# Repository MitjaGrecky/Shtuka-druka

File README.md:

# Shtuka Druka

An open, standalone desktop music instrument: synthesizer, sampler and DAW in one box.
The idea is improvising with sound from everywhere: capture audio from any source,
then shape it with filters and effects.

Status: design phase. Panel layout v7, enclosure, I/O, audio chain and compute platform are decided.
First board: M1 screen knobs module (being routed). Next: W1 Levels, then a 1:1 cardboard mockup.

## What is here

| Folder | Contents |
|---|---|
| `docs/ru/` | Research and design documents (Russian). Start with `README.md` (map of documents) and `decisions/README.md` — the single source of truth for every decision, split by topic |
| `bench/` | CPU benchmark: how many reference tracks a processor can run at 48 kHz / 128 samples |
| `mockup/` | 1:1 cardboard mockup templates (A4, PDF) and the script that generates them |
| `model3d/` | Interactive 3D model of panel v7, built from `mockup/layout/layout_v7.json` (open `index.html` in a browser; rebuild with `build_model3d_v7.py`) |
| `firmware/protocol/` | Board <-> computer protocol (SDP v0): C header for firmware and host |
| `tools/` | `sdp.py`: reference codec, self-test and frame monitor |
| `hardware/` | KiCad boards, generated from Python (`gen/`), checked by CI: `m1-screen-knobs` (first board), `w1-levels` |
| `notes/handoff.md` | Task queue between the cloud and local Claude sessions (rules in `CLAUDE.md`) |
| `.github/workflows/` | CI: ERC, DRC with schematic parity, BOM, Gerbers for every board on every push |

## Key facts

- 8x8 RGB pad grid, 16+ tracks (target 32-64), endless encoders with LED rings, 10.1" screen at 30 deg
- Body 515 x 460 mm, 68 mm high at the front, 143 mm at the rear, 30 deg slope for the screen, detachable wrist rest
- Inputs: 2 combo XLR/TRS, 2 Hi-Z, phono with RIAA, 8 line inputs, USB audio, 2-4 CV
- Converters: Cirrus Logic Pro (CS5308P/CS5304P ADC, CS4308P DAC), two-path inputs without a preamp chip
- Outputs: Main and Aux (balanced TRS), RCA copy of Main, 2 headphones
- MIDI: 2 in / 4 out DIN, 1 in / 2 out TRS (type A/B switchable); 8 CV/Gate, sync block, Ableton Link
- Compute: x86 on a Mini-ITX board (Intel N100 to start, 8-core upgrade on the same mounts)
- Two RP2350 boards (panel, control) over internal USB; audio board on two xcore.ai, USB Audio Class 2

## Licenses

- Software: GNU AGPL-3.0-or-later (`LICENSE`)
- Hardware: CERN-OHL-S-2.0 (`hardware/LICENSE`)

---

Штука Дрюка — открытый настольный инструмент: синтезатор, сэмплер и DAW в одном корпусе.
Документы проекта на русском лежат в `docs/ru/`, карта документов — `docs/ru/README.md`, все решения — в `docs/ru/decisions/` (начинать с `README.md`).

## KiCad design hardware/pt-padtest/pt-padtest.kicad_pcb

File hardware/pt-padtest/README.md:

# PT — тестовая плата пэдов 4 × 4 (R194, P120)

**Статус: rev 0.1 (26.11.2026) — схема и расстановка, без трассировки.** 2 слоя, 132 × 164 мм, 153 детали. Генераторы: `gen/footprints.py` (электроды и посадки светодиода в общую библиотеку), `gen/design.py`, `gen/make_sch.py`, `gen/make_pcb.py`. Проверки на ПК: ERC 0, DRC 0 ошибок (431 неразведённое), parity 0, `sch_netcheck` 0.

## Пэды: полный перебор 2 × 2 × 2, каждый вариант под ножки V1 и V3

Шаг 28 × 25, поле гребёнок 21 × 17, четыре зоны + общий электрод (рамка с пальцами). Столбцы 1–2 — ножка V1, 3–4 — V3.

| Ряд (спереди назад по плате) | Зоны | Прорезь под свет | Столбцы 1 и 3 | Столбцы 2 и 4 |
|---|---|---|---|---|
| 1 (пэды 1–4) | квадранты | 3,5 × 3,1 («3 мм») | 7 mil | 10 mil |
| 2 (5–8) | квадранты | 3,5 × 4,0 («4 мм») | 7 mil | 10 mil |
| 3 (9–12) | треугольники | 3,5 × 3,1 | 7 mil | 10 mil |
| 4 (13–16) | треугольники | 3,5 × 4,0 | 7 mil | 10 mil |

Проверено скриптом: каждый электрод — один кусок меди, зазор до общего ровно 0,179 / 0,255 мм, площади зон 19,7–22,3 мм². Маска открыта по всему полю, покрытие **ENIG**.

## Электроника

| Блок | Детали |
|---|---|
| Контроллер | Raspberry Pi Pico 2 модулем на штырях (USB); GPIO как на P2: GP0/1 I²C, GP16–19 SPI0, GP20–22 адрес мультиплексоров |
| Чтение 64 зон | как на P2: общий электрод на +3V3A, 10 кОм на зону, 8 × 74HC4051 → ADC128S102 (канал АЦП = мультиплексор, пэды по два: Y0–Y3 и Y4–Y7), 1 кОм + 1 нФ |
| Свет | 16 × GL6028RGB01-B (C51933363), снизу, в прорезь; LP5864, строки SW0–SW2 по 6 пэдов; 5 В от USB |

Прошивка LP5864: Max_Line_Num = 3, режим 1, 125 кГц, PWM_Phase_Shift (Dev_initial = 0x18, `notes/closing/led_noise.md`).

## Отличия от P120 и открытое

- **Отверстие не круглое.** Светодиод реверсивного монтажа стоит в прорези, круг Ø 3/4 мм вместе с ним не помещается. «3 мм» и «4 мм» — прорези 3,1 и 4,0 мм по y при ширине 3,5.
- **Посадка светодиода** — библиотечная EasyEDA/LCSC для C51933363; площадки укорочены с внутренней стороны (x 1,85 → 1,95), чтобы медь отстояла от прорези на 0,2 мм (в библиотеке 0,1). **Даташита нет** (JLC не отдаёт): не подтверждены цвета катодов 1/2/4 (прошивка переназначит), высота корпуса и выступ линзы над платой (дизайнеру: выемка в ножке Ø 6). PDF GL6028RGB01-B — в список пользователю.
- Наличие на 26.11.2026 (JLC): C51933363 ≈ 7100 шт.
- Не разведена; допуски фрезеровки прорезей и поведение XactFSR не проверялись.
- `pcb_geomcheck` пишет «courtyard outside the outline» для пэдов и светодиодов: это внутренние прорези, ложное срабатывание.

License: CERN-OHL-S-2.0 (hardware), AGPL-3.0-or-later (code).

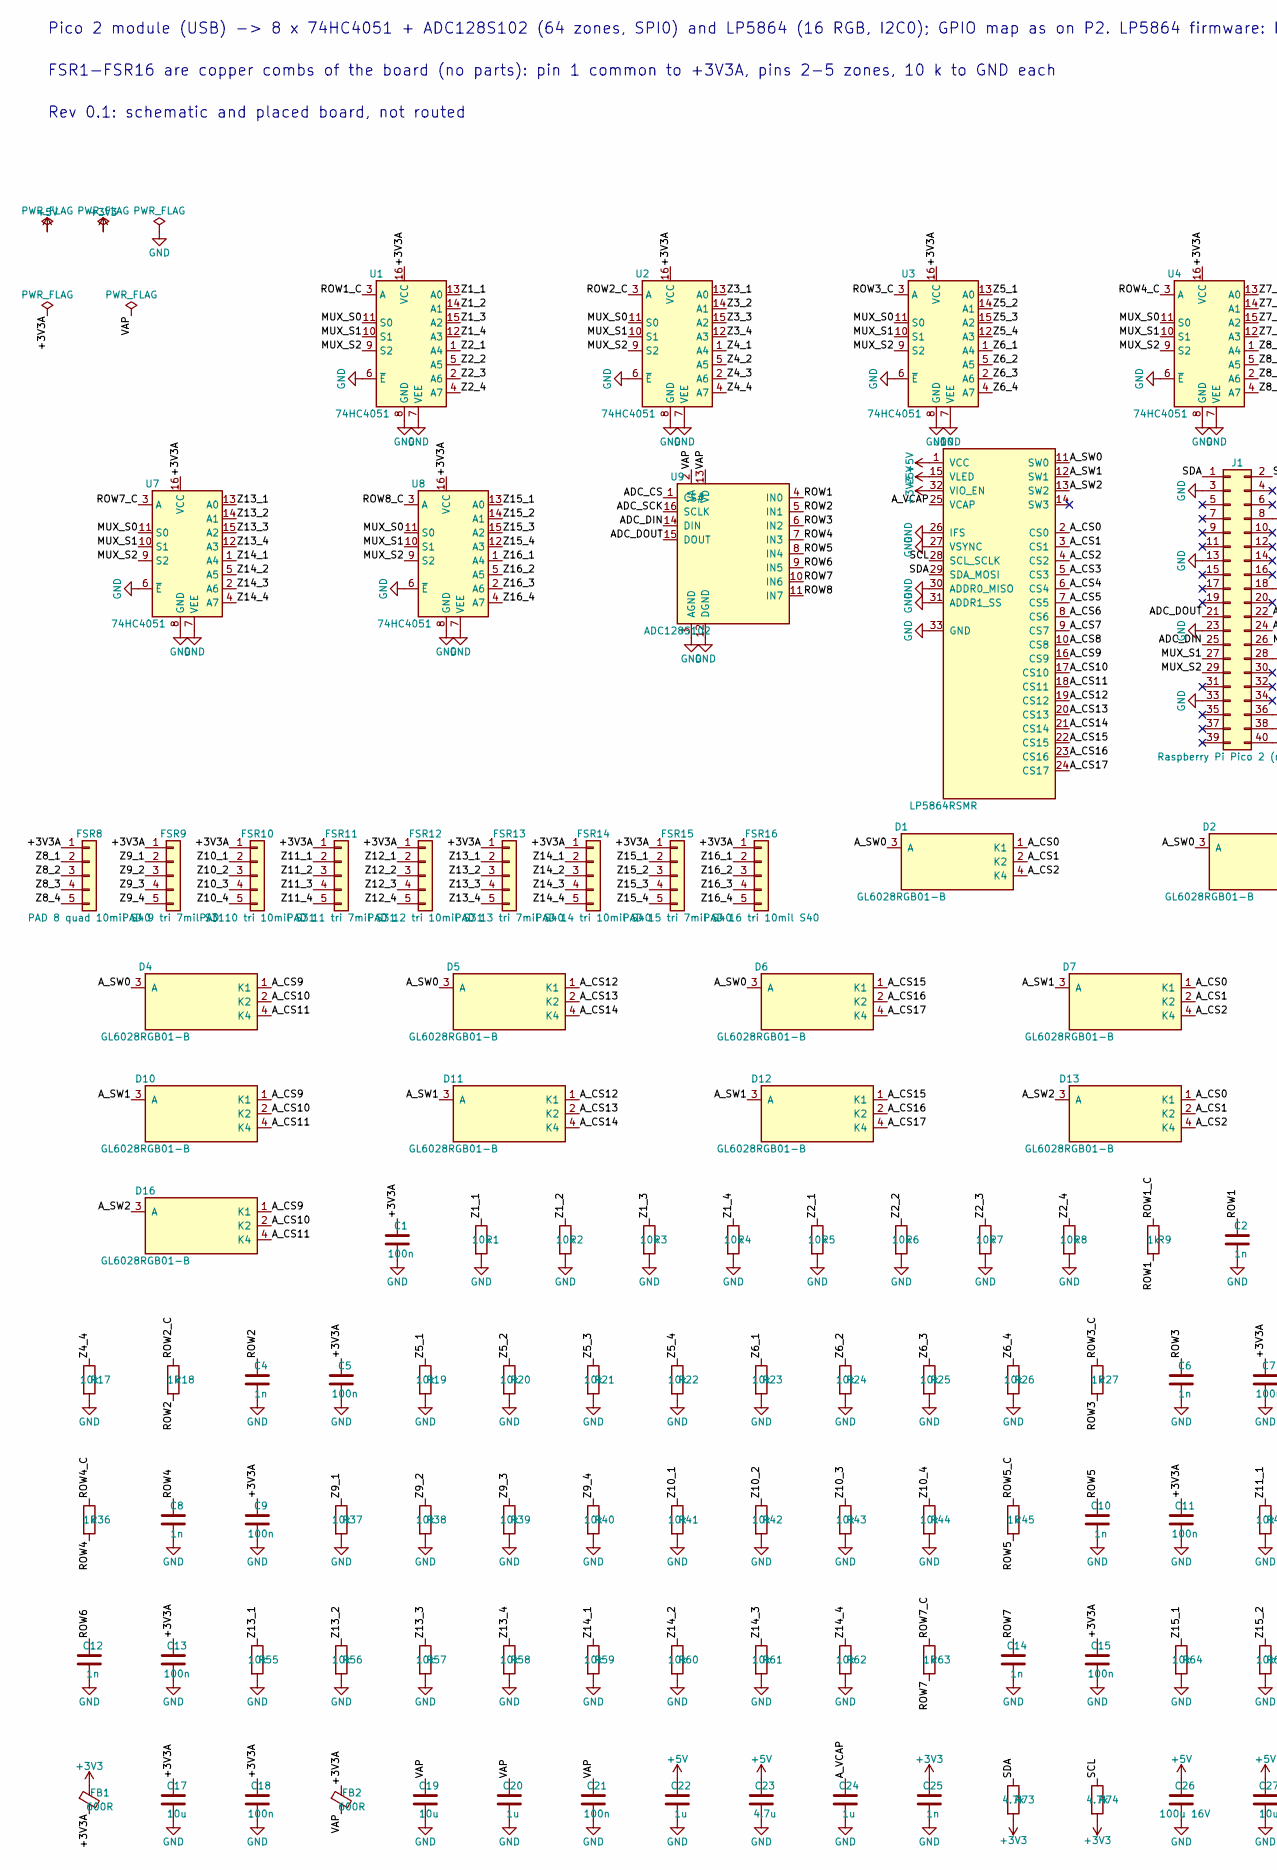
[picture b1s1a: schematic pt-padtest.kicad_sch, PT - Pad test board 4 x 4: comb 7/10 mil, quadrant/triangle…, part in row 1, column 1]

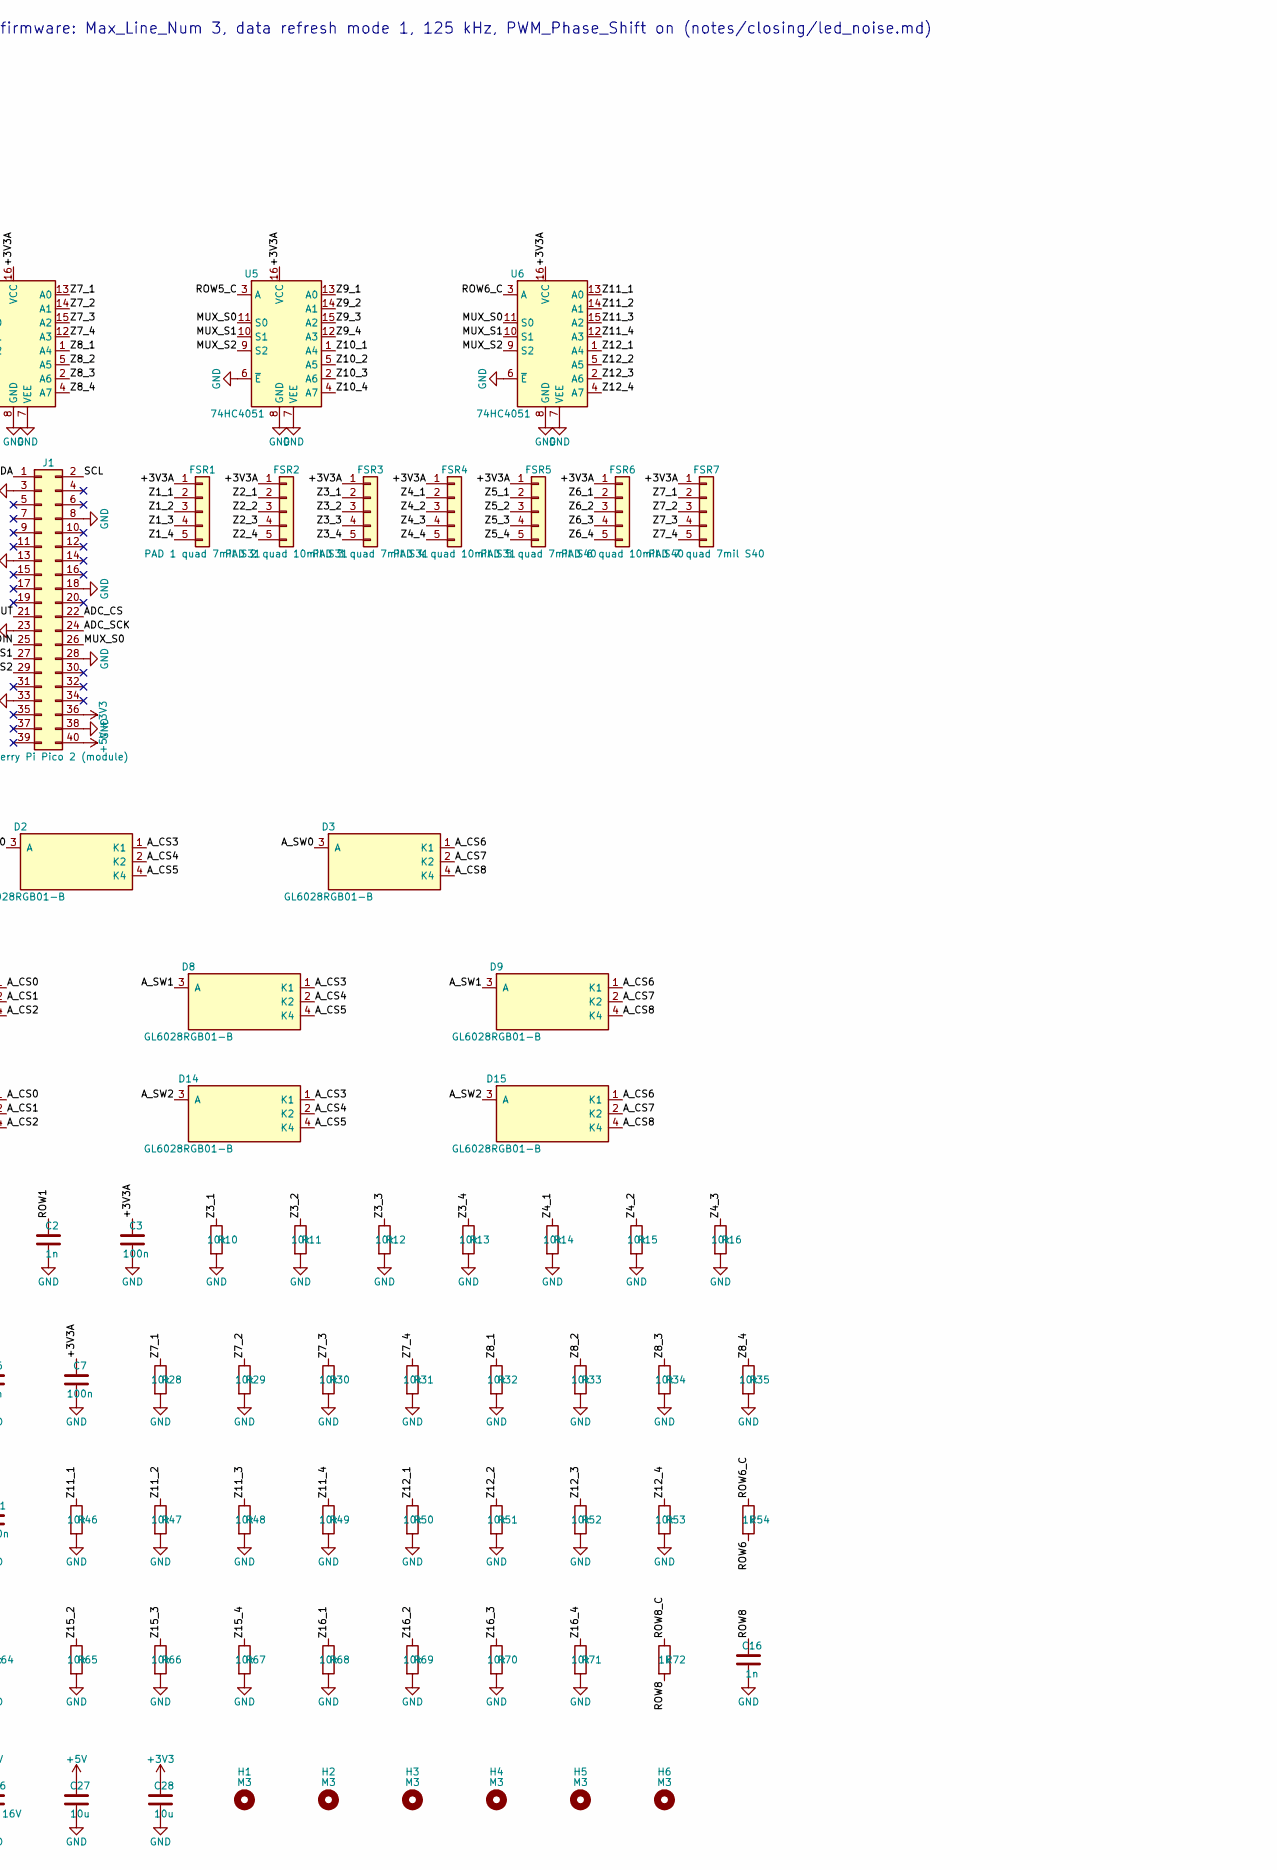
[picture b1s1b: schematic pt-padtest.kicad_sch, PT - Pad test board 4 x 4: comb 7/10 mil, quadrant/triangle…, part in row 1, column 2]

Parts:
C1, C3, C5, C7, C9, C11, C13, C15, C18, C21: 100n; C_0402_1005Metric; LCSC C1525
C2, C4, C6, C8, C10, C12, C14, C16, C25: 1n; C_0402_1005Metric; LCSC C1523
C17, C19, C27, C28: 10u; C_0805_2012Metric; LCSC C15850
C20, C22, C24: 1u; C_0402_1005Metric; LCSC C52923
C23: 4.7u; C_0805_2012Metric; LCSC C1779
C26: 100u 16V; CP_Elec_6.3x5.4; LCSC C7469977
D1, D2, D3, D4, D9, D10, D11, D12: GL6028RGB01-B; LED_RGB_6028_ReverseMount_C51933363_slot31; LCSC C51933363
D5, D6, D7, D8, D13, D14, D15, D16: GL6028RGB01-B; LED_RGB_6028_ReverseMount_C51933363_slot40; LCSC C51933363
FB1, FB2: 600R; R_0603_1608Metric; LCSC C14709
FSR1: PAD 1 quad 7mil S31; PT44_comb_quad_7mil_slot31
FSR2: PAD 2 quad 10mil S31; PT44_comb_quad_10mil_slot31
FSR3: PAD 3 quad 7mil S31; PT44_comb_quad_7mil_slot31
FSR4: PAD 4 quad 10mil S31; PT44_comb_quad_10mil_slot31
FSR5: PAD 5 quad 7mil S40; PT44_comb_quad_7mil_slot40
FSR6: PAD 6 quad 10mil S40; PT44_comb_quad_10mil_slot40
FSR7: PAD 7 quad 7mil S40; PT44_comb_quad_7mil_slot40
FSR8: PAD 8 quad 10mil S40; PT44_comb_quad_10mil_slot40
FSR9: PAD 9 tri 7mil S31; PT44_comb_tri_7mil_slot31
FSR10: PAD 10 tri 10mil S31; PT44_comb_tri_10mil_slot31
FSR11: PAD 11 tri 7mil S31; PT44_comb_tri_7mil_slot31
FSR12: PAD 12 tri 10mil S31; PT44_comb_tri_10mil_slot31
FSR13: PAD 13 tri 7mil S40; PT44_comb_tri_7mil_slot40
FSR14: PAD 14 tri 10mil S40; PT44_comb_tri_10mil_slot40
FSR15: PAD 15 tri 7mil S40; PT44_comb_tri_7mil_slot40
FSR16: PAD 16 tri 10mil S40; PT44_comb_tri_10mil_slot40
H1, H2, H3, H4, H5, H6: M3; MountingHole_3.2mm_M3_ISO7380
J1: Raspberry Pi Pico 2 (module); RaspberryPi_Pico_Common_THT
R1, R2, R3, R4, R5, R6, R7, R8, R10, R11, R12, R13, R14, R15, R16, R17, R19, R20, R21, R22, R23, R24, R25, R26, R28, R29, R30, R31, R32, R33, R34, R35, R37, R38, R39, R40, R41, R42, R43, R44, R46, R47, R48, R49, R50, R51, R52, R53, R55, R56, R57, R58, R59, R60, R61, R62, R64, R65, R66, R67, R68, R69, R70, R71: 10k; R_0402_1005Metric; LCSC C25744
R9, R18, R27, R36, R45, R54, R63, R72: 1k; R_0402_1005Metric; LCSC C11702
R73, R74: 4.7k; R_0402_1005Metric; LCSC C25900
U1, U2, U3, U4, U5, U6, U7, U8: 74HC4051; TSSOP-16_4.4x5mm_P0.65mm; LCSC C5645
U9: ADC128S102; TSSOP-16_4.4x5mm_P0.65mm; LCSC C206503
U10: LP5864RSMR; VQFN-32-1EP_4x4mm_P0.4mm_EP2.8x2.8mm; LCSC C5220564

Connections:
+3V3: C25.1, C28.1, FB1.1, J1.36, R73.2, R74.2, U10.32 (VIO_EN)
+5V: C22.1, C23.1, C26.1, C27.1, J1.40, U10.1 (VCC), U10.15 (VLED)
/+3V3A: C1.1, C3.1, C5.1, C7.1, C9.1, C11.1, C13.1, C15.1, C17.1, C18.1, FB1.2, FB2.1, FSR1.1, FSR2.1, FSR3.1, FSR4.1, FSR5.1, FSR6.1, FSR7.1, FSR8.1, FSR9.1, FSR10.1, FSR11.1, FSR12.1, FSR13.1, FSR14.1, FSR15.1, FSR16.1, U1.16 (VCC), U2.16 (VCC), U3.16 (VCC), U4.16 (VCC), U5.16 (VCC), U6.16 (VCC), U7.16 (VCC), U8.16 (VCC)
/ADC_CS: J1.22, U9.1 (CS#)
/ADC_DIN: J1.25, U9.14 (DIN)
/ADC_DOUT: J1.21, U9.15 (DOUT)
/ADC_SCK: J1.24, U9.16 (SCLK)
/A_CS0: D1.1 (K1), D7.1 (K1), D13.1 (K1), U10.2 (CS0)
/A_CS1: D1.2 (K2), D7.2 (K2), D13.2 (K2), U10.3 (CS1)
/A_CS2: D1.4 (K4), D7.4 (K4), D13.4 (K4), U10.4 (CS2)
/A_CS3: D2.1 (K1), D8.1 (K1), D14.1 (K1), U10.5 (CS3)
/A_CS4: D2.2 (K2), D8.2 (K2), D14.2 (K2), U10.6 (CS4)
/A_CS5: D2.4 (K4), D8.4 (K4), D14.4 (K4), U10.7 (CS5)
/A_CS6: D3.1 (K1), D9.1 (K1), D15.1 (K1), U10.8 (CS6)
/A_CS7: D3.2 (K2), D9.2 (K2), D15.2 (K2), U10.9 (CS7)
/A_CS8: D3.4 (K4), D9.4 (K4), D15.4 (K4), U10.10 (CS8)
/A_CS9: D4.1 (K1), D10.1 (K1), D16.1 (K1), U10.16 (CS9)
/A_CS10: D4.2 (K2), D10.2 (K2), D16.2 (K2), U10.17 (CS10)
/A_CS11: D4.4 (K4), D10.4 (K4), D16.4 (K4), U10.18 (CS11)
/A_CS12: D5.1 (K1), D11.1 (K1), U10.19 (CS12)
/A_CS13: D5.2 (K2), D11.2 (K2), U10.20 (CS13)
/A_CS14: D5.4 (K4), D11.4 (K4), U10.21 (CS14)
/A_CS15: D6.1 (K1), D12.1 (K1), U10.22 (CS15)
/A_CS16: D6.2 (K2), D12.2 (K2), U10.23 (CS16)
/A_CS17: D6.4 (K4), D12.4 (K4), U10.24 (CS17)
/A_SW0: D1.3 (A), D2.3 (A), D3.3 (A), D4.3 (A), D5.3 (A), D6.3 (A), U10.11 (SW0)
/A_SW1: D7.3 (A), D8.3 (A), D9.3 (A), D10.3 (A), D11.3 (A), D12.3 (A), U10.12 (SW1)
/A_SW2: D13.3 (A), D14.3 (A), D15.3 (A), D16.3 (A), U10.13 (SW2)
/A_VCAP: C24.1, U10.25 (VCAP)
/MUX_S0: J1.26, U1.11 (S0), U2.11 (S0), U3.11 (S0), U4.11 (S0), U5.11 (S0), U6.11 (S0), U7.11 (S0), U8.11 (S0)
/MUX_S1: J1.27, U1.10 (S1), U2.10 (S1), U3.10 (S1), U4.10 (S1), U5.10 (S1), U6.10 (S1), U7.10 (S1), U8.10 (S1)
/MUX_S2: J1.29, U1.9 (S2), U2.9 (S2), U3.9 (S2), U4.9 (S2), U5.9 (S2), U6.9 (S2), U7.9 (S2), U8.9 (S2)
/ROW1: C2.1, R9.2, U9.4 (IN0)
/ROW1_C: R9.1, U1.3 (A)
/ROW2: C4.1, R18.2, U9.5 (IN1)
/ROW2_C: R18.1, U2.3 (A)
/ROW3: C6.1, R27.2, U9.6 (IN2)
/ROW3_C: R27.1, U3.3 (A)
/ROW4: C8.1, R36.2, U9.7 (IN3)
/ROW4_C: R36.1, U4.3 (A)
/ROW5: C10.1, R45.2, U9.8 (IN4)
/ROW5_C: R45.1, U5.3 (A)
/ROW6: C12.1, R54.2, U9.9 (IN5)
/ROW6_C: R54.1, U6.3 (A)
/ROW7: C14.1, R63.2, U9.10 (IN6)
/ROW7_C: R63.1, U7.3 (A)
/ROW8: C16.1, R72.2, U9.11 (IN7)
/ROW8_C: R72.1, U8.3 (A)
/SCL: J1.2, R74.1, U10.28 (SCL_SCLK)
/SDA: J1.1, R73.1, U10.29 (SDA_MOSI)
/VAP: C19.1, C20.1, C21.1, FB2.2, U9.2 (VA), U9.13 (VD)
/Z1_1: FSR1.2, R1.1, U1.13 (A0)
/Z1_2: FSR1.3, R2.1, U1.14 (A1)
/Z1_3: FSR1.4, R3.1, U1.15 (A2)
/Z1_4: FSR1.5, R4.1, U1.12 (A3)
/Z2_1: FSR2.2, R5.1, U1.1 (A4)
/Z2_2: FSR2.3, R6.1, U1.5 (A5)
/Z2_3: FSR2.4, R7.1, U1.2 (A6)
/Z2_4: FSR2.5, R8.1, U1.4 (A7)
/Z3_1: FSR3.2, R10.1, U2.13 (A0)
/Z3_2: FSR3.3, R11.1, U2.14 (A1)
/Z3_3: FSR3.4, R12.1, U2.15 (A2)
/Z3_4: FSR3.5, R13.1, U2.12 (A3)
/Z4_1: FSR4.2, R14.1, U2.1 (A4)
/Z4_2: FSR4.3, R15.1, U2.5 (A5)
/Z4_3: FSR4.4, R16.1, U2.2 (A6)
/Z4_4: FSR4.5, R17.1, U2.4 (A7)
/Z5_1: FSR5.2, R19.1, U3.13 (A0)
/Z5_2: FSR5.3, R20.1, U3.14 (A1)
/Z5_3: FSR5.4, R21.1, U3.15 (A2)
/Z5_4: FSR5.5, R22.1, U3.12 (A3)
/Z6_1: FSR6.2, R23.1, U3.1 (A4)
/Z6_2: FSR6.3, R24.1, U3.5 (A5)
/Z6_3: FSR6.4, R25.1, U3.2 (A6)
/Z6_4: FSR6.5, R26.1, U3.4 (A7)
/Z7_1: FSR7.2, R28.1, U4.13 (A0)
/Z7_2: FSR7.3, R29.1, U4.14 (A1)
/Z7_3: FSR7.4, R30.1, U4.15 (A2)
/Z7_4: FSR7.5, R31.1, U4.12 (A3)
/Z8_1: FSR8.2, R32.1, U4.1 (A4)
/Z8_2: FSR8.3, R33.1, U4.5 (A5)
/Z8_3: FSR8.4, R34.1, U4.2 (A6)
/Z8_4: FSR8.5, R35.1, U4.4 (A7)
/Z9_1: FSR9.2, R37.1, U5.13 (A0)
/Z9_2: FSR9.3, R38.1, U5.14 (A1)
/Z9_3: FSR9.4, R39.1, U5.15 (A2)
/Z9_4: FSR9.5, R40.1, U5.12 (A3)
/Z10_1: FSR10.2, R41.1, U5.1 (A4)
/Z10_2: FSR10.3, R42.1, U5.5 (A5)
/Z10_3: FSR10.4, R43.1, U5.2 (A6)
/Z10_4: FSR10.5, R44.1, U5.4 (A7)
/Z11_1: FSR11.2, R46.1, U6.13 (A0)
/Z11_2: FSR11.3, R47.1, U6.14 (A1)
/Z11_3: FSR11.4, R48.1, U6.15 (A2)
/Z11_4: FSR11.5, R49.1, U6.12 (A3)
/Z12_1: FSR12.2, R50.1, U6.1 (A4)
/Z12_2: FSR12.3, R51.1, U6.5 (A5)
/Z12_3: FSR12.4, R52.1, U6.2 (A6)
/Z12_4: FSR12.5, R53.1, U6.4 (A7)
/Z13_1: FSR13.2, R55.1, U7.13 (A0)
/Z13_2: FSR13.3, R56.1, U7.14 (A1)
/Z13_3: FSR13.4, R57.1, U7.15 (A2)
/Z13_4: FSR13.5, R58.1, U7.12 (A3)
/Z14_1: FSR14.2, R59.1, U7.1 (A4)
/Z14_2: FSR14.3, R60.1, U7.5 (A5)
/Z14_3: FSR14.4, R61.1, U7.2 (A6)
/Z14_4: FSR14.5, R62.1, U7.4 (A7)
/Z15_1: FSR15.2, R64.1, U8.13 (A0)
/Z15_2: FSR15.3, R65.1, U8.14 (A1)
/Z15_3: FSR15.4, R66.1, U8.15 (A2)
/Z15_4: FSR15.5, R67.1, U8.12 (A3)
/Z16_1: FSR16.2, R68.1, U8.1 (A4)
/Z16_2: FSR16.3, R69.1, U8.5 (A5)
/Z16_3: FSR16.4, R70.1, U8.2 (A6)
/Z16_4: FSR16.5, R71.1, U8.4 (A7)
GND: C1.2, C2.2, C3.2, C4.2, C5.2, C6.2, C7.2, C8.2, C9.2, C10.2, C11.2, C12.2, C13.2, C14.2, C15.2, C16.2, C17.2, C18.2, C19.2, C20.2, C21.2, C22.2, C23.2, C24.2, C25.2, C26.2, C27.2, C28.2, J1.3, J1.8, J1.13, J1.18, J1.23, J1.28, J1.33, J1.38, R1.2, R2.2, R3.2, R4.2, R5.2, R6.2, R7.2, R8.2, R10.2, R11.2, R12.2, R13.2, R14.2, R15.2, R16.2, R17.2, R19.2, R20.2, R21.2, R22.2, R23.2, R24.2, R25.2, R26.2, R28.2, R29.2, R30.2, R31.2, R32.2, R33.2, R34.2, R35.2, R37.2, R38.2, R39.2, R40.2, R41.2, R42.2, R43.2, R44.2, R46.2, R47.2, R48.2, R49.2, R50.2, R51.2, R52.2, R53.2, R55.2, R56.2, R57.2, R58.2, R59.2, R60.2, R61.2, R62.2, R64.2, R65.2, R66.2, R67.2, R68.2, R69.2, R70.2, R71.2, U1.6 (~E), U1.7 (VEE), U1.8 (GND), U2.6 (~E), U2.7 (VEE), U2.8 (GND), U3.6 (~E), U3.7 (VEE), U3.8 (GND), U4.6 (~E), U4.7 (VEE), U4.8 (GND), U5.6 (~E), U5.7 (VEE), U5.8 (GND), U6.6 (~E), U6.7 (VEE), U6.8 (GND), U7.6 (~E), U7.7 (VEE), U7.8 (GND), U8.6 (~E), U8.7 (VEE), U8.8 (GND), U9.3 (AGND), U9.12 (DGND), U10.26 (IFS), U10.27 (VSYNC), U10.30 (ADDR0_MISO), U10.31 (ADDR1_SS), U10.33 (GND)

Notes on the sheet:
Pico 2 module (USB) -> 8 x 74HC4051 + ADC128S102 (64 zones, SPI0) and LP5864 (16 RGB, I2C0); GPIO map as on P2. LP5864 firmware: Max_Line_Num 3, data refresh mode 1, 125 kHz, PWM_Phase_Shift on (notes/closing/led_noise.md)
FSR1-FSR16 are copper combs of the board (no parts): pin 1 common to +3V3A, pins 2-5 zones, 10 k to GND each
Rev 0.1: schematic and placed board, not routed

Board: 2 copper layers, 153 parts (18 on the bottom side), 116 nets, no tracks yet.

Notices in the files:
hardware/m1-screen-knobs/almost/m1-screen-knobs.kicad_sch:
Shtuka Druka - open hardware, CERN-OHL-S-2.0
hardware/m1-screen-knobs/m1-screen-knobs.kicad_pcb:
M1 rev 0.5  CERN-OHL-S-2.0
hardware/m3-tempo-swing/m3-tempo-swing.kicad_pcb:
Shtuka Druka  CERN-OHL-S-2.0
